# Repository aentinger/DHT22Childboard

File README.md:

💾 DHT22 Childboard
====================

# 📸 Image

# 📂 Description

The LXRobotics DHT22 Humidity/Temperature Sensor Childboard is based on the known DHT22 sensor and allows the measurement of temperature and of the air humidity. For a quick and easy start, an open source Arduino library with sample programs is available.

**Features**

* Measurement of Temperature and Air Humidity
* Red Status-LED controlled by user
* Can be used with the Radioshield the Childboard Adaptershield
* Arduino Library with example programs is available on GitHub

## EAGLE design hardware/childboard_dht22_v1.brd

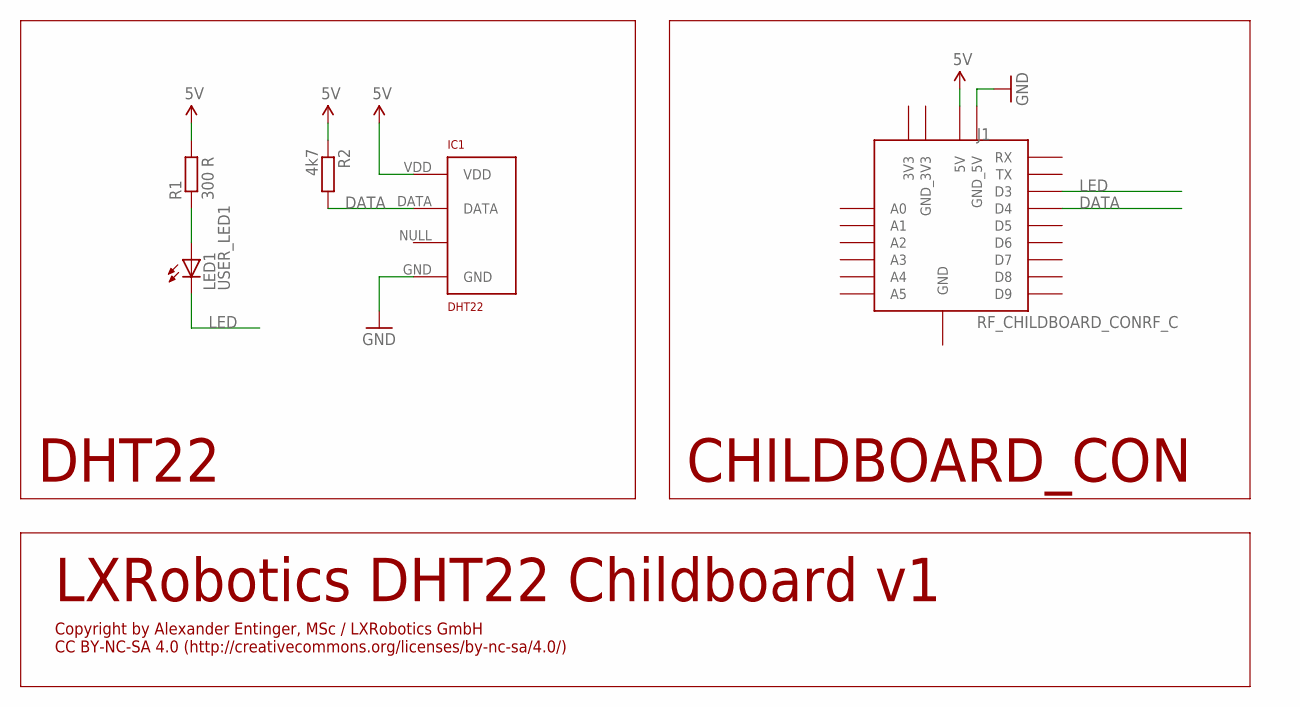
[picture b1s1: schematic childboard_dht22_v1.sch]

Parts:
IC1: DHT22; RHT03_DHT-22/RA
J1: RF_CHILDBOARD_CONRF_C; RF_CHILDBOARD_CON
LED1: USER_LED1; LED5MM
R1: 300 R; 0204/7
R2: 4k7; 0204/7

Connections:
5V: IC1.VDD, J1.5V, R1.2, R2.1
DATA: IC1.DATA, J1.D4, R2.2
GND: IC1.GND, J1.GND_5V
LED: J1.D3, LED1.K (C)
unnamed: LED1.A, R1.1

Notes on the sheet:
DHT22
CHILDBOARD_CON
LXRobotics DHT22 Childboard v1
Copyright by Alexander Entinger, MSc / LXRobotics GmbH CC BY-NC-SA 4.0 (http://creativecommons.org/licenses/by-nc-sa/4.0/)

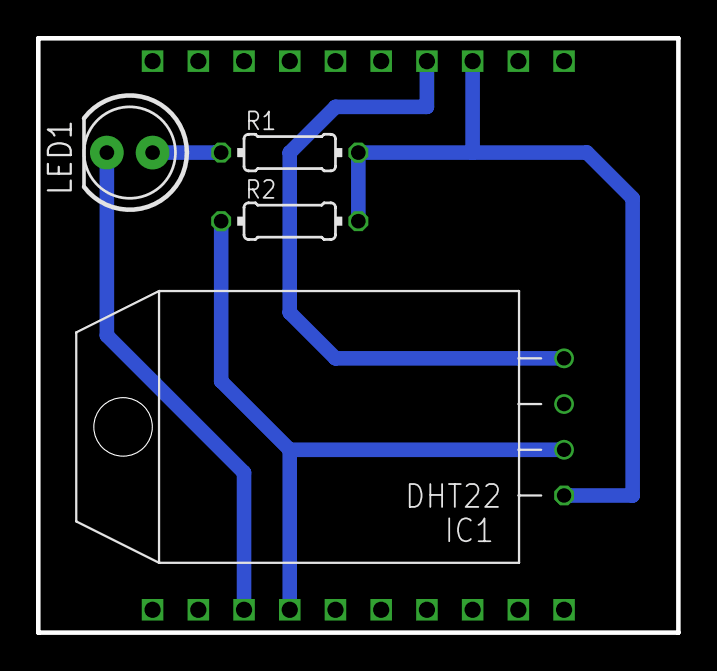
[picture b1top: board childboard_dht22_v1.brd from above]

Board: 2 copper layers, 35.6 x 33.0 mm, 5 parts (0 on the bottom side), 5 nets.

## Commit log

2017-06-27 Adding hardware + images
2025-03-26 Add BOM.
2025-03-26 Pretty up README.

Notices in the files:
README.md:
License: CC BY-NC-SA 4.0
parts and their libraries:
SparkFun-LED: Licensing: CC v3.0 Share-Alike You are welcome to use this library for commercial purposes.
